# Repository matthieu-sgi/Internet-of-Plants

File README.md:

# Internet of Plants

The **Internet of Plants** is an innovative project that revolutionizes the way we interact with and monitor plants. By transforming plants into living sensors, we create a bridge between nature and technology. In this project, we utilize the interaction (touch) you have with the plant and its humidity level to generate real-time sonification of the data. This not only enriches our connection with nature but also provides valuable insights into plant health and well-being.

## Table of Contents

- [Introduction](#introduction)
- [Project Overview](#project-overview)
- [Hardware](#hardware)
- [Software](#software)
- [Internet and networking](#internet-and-networking)
- [Roadmap](#roadmap)

## Introduction

The Internet of Plants is a creative exploration into the realm of biotechnology and sensory augmentation. It enables us to perceive and interpret data from the natural world in a novel and engaging way. With this project, we hope to inspire a deeper appreciation for the environment and promote sustainable practices through data-driven insights. This by conducting a musical art experience.

## Project Overview

### How it Works

The core concept of the Internet of Plants is to use plants as living sensors. We collect data from the plants through two main channels:

1. **Interaction (Touch):** When you interact with a plant by touching its leaves or stems, the project senses this interaction and translates it into a unique sound.

2. **Humidity Level:** We monitor the humidity level of the soil. Changes in humidity are reflected through a different set of sounds, providing valuable feedback on the plant's environmental conditions.

### Repository Structure

    Internet of Plants/
    |-- README.md
    |-- software/
    |   |-- [Software files and source code]
    |-- hardware/
    |   |-- [Hardware design files]
    |-- media/
    |   |-- [Image files related to the project]
    |-- documentation/
    |   |-- poster/
    |   |   |-- [Poster files]
    |   |-- BOM/ # Bill of Materials
    |   |   └── pcb_bom_iop_budget.csv # BOM for the PCB and the budget
    |   |-- user_study/
    |   └──   |-- [User study files]
    └── acknowledgements.md

## Hardware

The hardware for the Internet of Plants is based on a custom-designed Printed Circuit Board (PCB). You can find detailed information about the PCB design, components, and assembly in the **PCB** folder of this repository.

## Software

The software component of this project is responsible for collecting data from the plant sensors and converting it into sonified feedback. It involves signal processing, data visualization, and sound synthesis. Detailed instructions on setting up and running the software can be found in the **Software** section of this repository.

## Internet and networking

The PCBs are made out of an ESP32, a MCU that has Wifi capabilities. The ESP32 is connected to a server that runs a Pure Data. The Pure Data patch is responsible for the sonification of the data.
This allows to connect several and many plants to the same server and to have a centralized sonification of the data.
This is done in order to do a musical art experience and to go to Ars Electronica with the project.

## Roadmap

- [x] Test the electronic filter for the touch interaction
- [x] Test the sound amplification circuit
- [x] Build a prototyping PCB
- [x] Build a software embedded synthesizer
- [x] Do sonification with the prototyping PCB
- [x] Build the "Internet"
- [ ] Build the final PCB
- [x] Build the PureData patch on server
- [ ] Check the correlation between humidity and sensor values
- [x] play some sound from the micro sd
- [ ] check on the maths (the EMA is working well, the ema_std not so much)

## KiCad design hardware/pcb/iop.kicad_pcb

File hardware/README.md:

# Hardware Directory

## Directory Structure

    hardware/
    |-- README.md
    |-- PCB/
    |   |-- [Full KiCad Project Files]
    |-- PCB Devkit/
    |   |-- [Full KiCad Project Files]

Overview

 - [PCB](https://github.com/matthieu-sgi/Internet-of-Plants/tree/main/hardware/pcb): Final version of hardware. Currently in development.
 - [PCB Devkit](https://github.com/matthieu-sgi/Internet-of-Plants/tree/main/hardware/pcb_devkit): ESP32 WROOM 32 Devkit for rapid prototyping. First version of hardware. Not in development anymore.

## TO DO:

- [ ] Fix the pcb devkit
- [ ] Finish the main pcb

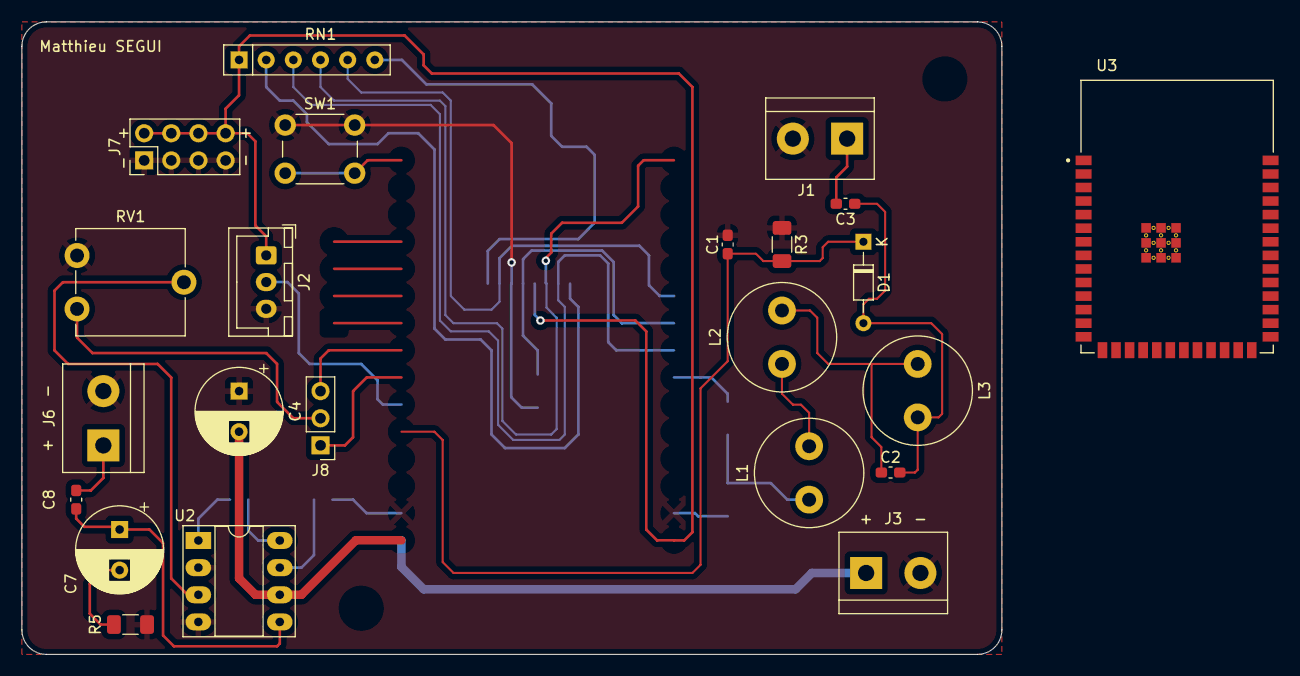
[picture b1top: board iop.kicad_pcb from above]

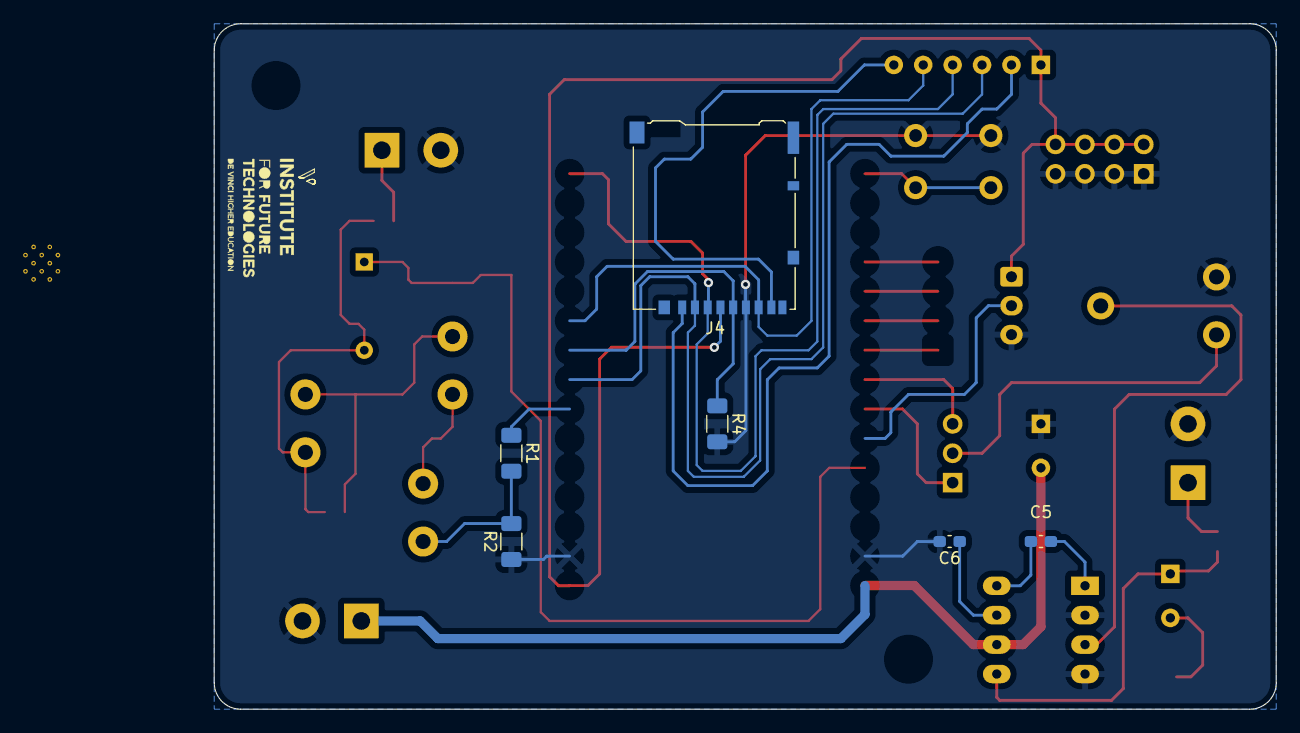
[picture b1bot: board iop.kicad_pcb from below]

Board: 2 copper layers, 91.7 x 59.2 mm, 29 parts (6 on the bottom side), 24 nets.

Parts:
C1: 100pF; C_0603_1608Metric_Pad1.08x0.95mm_HandSolder
C2: 1nF; C_0603_1608Metric_Pad1.08x0.95mm_HandSolder
C3, C6: 10nF; C_0603_1608Metric_Pad1.08x0.95mm_HandSolder
C4: 100μF; CP_Radial_D8.0mm_P3.80mm
C5, C8: 10μF; C_0603_1608Metric_Pad1.08x0.95mm_HandSolder
C7: 47μF; CP_Radial_D8.0mm_P3.80mm
D1: D; D_DO-34_SOD68_P7.62mm_Horizontal
J1: plant_connector; TerminalBlock_bornier-2_P5.08mm
J2: moisture_sensor_conn; JST_XH_B3B-XH-A_1x03_P2.50mm_Vertical
J3: power_input; TerminalBlock_bornier-2_P5.08mm
J4: micro_sd_slot; microSD_HC_Hirose_DM3AT-SF-PEJM5
J6: speaker_output; TerminalBlock_bornier-2_P5.08mm
J7: ext_pwr_output; PinHeader_2x04_P2.54mm_Vertical
J8: jmp_dacs; PinHeader_1x03_P2.54mm_Vertical
L1, L2, L3: 3.3mH; L_Radial_D10.0mm_P5.00mm_Fastron_07P
R1: 10kΩ; R_1206_3216Metric_Pad1.30x1.75mm_HandSolder
R2: 4.7kΩ; R_1206_3216Metric_Pad1.30x1.75mm_HandSolder
R3: 1MΩ; R_1206_3216Metric_Pad1.30x1.75mm_HandSolder
R4: 100kΩ; R_1206_3216Metric_Pad1.30x1.75mm_HandSolder
R5: 10Ω; R_1206_3216Metric_Pad1.30x1.75mm_HandSolder
RN1: 100kΩ; R_Array_SIP6
RV1: R_Potentiometer; Potentiometer_ACP_CA9-V10_Vertical
SW1: SW_Push; SW_PUSH_6mm
U2: LM386; DIP-8_W7.62mm_Socket_LongPads
U3: ESP32-S3-WROOM-1-N8R8; XCVR_ESP32S3WROOM1N8R8

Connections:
+3V3: J2.1, J4.4, J7.2, J7.4, J7.6, J7.8, RN1.1 (common)
+5V: C4.2, J3.1, U2.6 (V+)
/CLK: J4.5, R4.1
/CS: J4.2, RN1.3 (R2)
/MISO: J4.7, RN1.5 (R4)
/MOSI: J4.3, RN1.4 (R3)
/audio_circuit/sound_input: J8.2, RV1.1
/plant_response: C1.1, D1.1 (K), R3.2
GND: C1.2, C4.1, C6.2, J1.2, J2.3, J3.2, J4.6, J6.2, J7.1, J7.3, J7.5, J7.7, R2.1, R3.1, R4.2, R5.2, RV1.3, SW1.1, U2.2 (-), U2.4 (GND)
unnamed: C2.1, L2.2, L3.1
unnamed: C5.1, U2.1 (GAIN)
unnamed: C5.2, U2.8 (GAIN)
unnamed: C7.1, C8.1, U2.5
unnamed: C7.2, R5.1
unnamed: C2.2, C3.1, D1.2 (A), L3.2
unnamed: C3.2, J1.1
unnamed: J4.1, RN1.2 (R1)
unnamed: J4.8, RN1.6 (R5)
unnamed: C8.2, J6.1
unnamed: L1.1, R1.2, R2.2
unnamed: L1.2, L2.1
unnamed: RV1.2, U2.3 (+)
unnamed: C6.1, U2.7 (BYPASS)
unnamed: U3.1 (GND), U3.40 (GND), U3.41_1 (GND), U3.41_2 (GND), U3.41_3 (GND), U3.41_4 (GND), U3.41_5 (GND), U3.41_6 (GND), U3.41_7 (GND), U3.41_8 (GND), U3.41_9 (GND)

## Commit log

2023-10-06 Adding media
2023-10-09 Adding README
2023-10-10 Modified roadmap
2023-10-23 Merging the tests
2023-11-09 Plotting the values
2023-11-23 Adding new dev branch
2023-11-24 Adding new version
2023-11-27 Testing a lot
2023-11-28 tested all my cpp functions
2023-11-28 FIXED THE BUG
2023-12-04 Cleaning the example code for first demo
2023-12-04 Cleaning the working tree
2023-12-04 Updating README
2023-12-14 Patched PD patch
2023-12-18 Updating the lib test.
    This in order to check on math
2023-12-18 Adding the maths lib for usage.
2023-12-18 Pushing minor changes
2023-12-18 Updating READMEs
2023-12-21 Updated the task list
2024-01-04 Updated lib
2024-01-10 New PCB version
2024-01-11 Updating PCB
2024-01-15 Working with music
2024-01-17 Adding the server side
2024-01-17 Added server
2024-01-18 Keeping pcb devkit
2024-01-18 Adding more media
2024-01-18 Adding documentation
2024-01-18 Adding acknowledgements
2024-01-18 Updated gitignore
2024-01-18 Adding README in hardware
2024-01-18 Cleaning
2024-01-18 Updating READMEs and cleaning stuff
2024-01-18 Adding budget and BOM
2024-01-19 Fixing bug
2024-01-21 Added auto setup of the server
2024-01-21 Adding deployment tuto
2024-01-22 Fixed the start.sh
2024-01-22 Fixed
2024-01-22 Update main
2024-01-23 Maintenance
2024-01-25 Added diagram software architecture
2024-01-25 More doc
2024-03-06 Adding the possibility to reuse socket
2024-03-06 Adding the path
2024-03-27 Fix address already used
2024-03-27 Update doc
2024-04-09 fix(user_study): Fix user study
2024-04-09 feat(codeowners): Add CODEOWNERS
2024-10-05 Adding all PDF to git LFS
2024-10-05 Install script updating templating files
2024-10-05 Updating link from DVIC to IFT
2024-10-13 master thesis stuff
2024-10-15 Work for master thesis
